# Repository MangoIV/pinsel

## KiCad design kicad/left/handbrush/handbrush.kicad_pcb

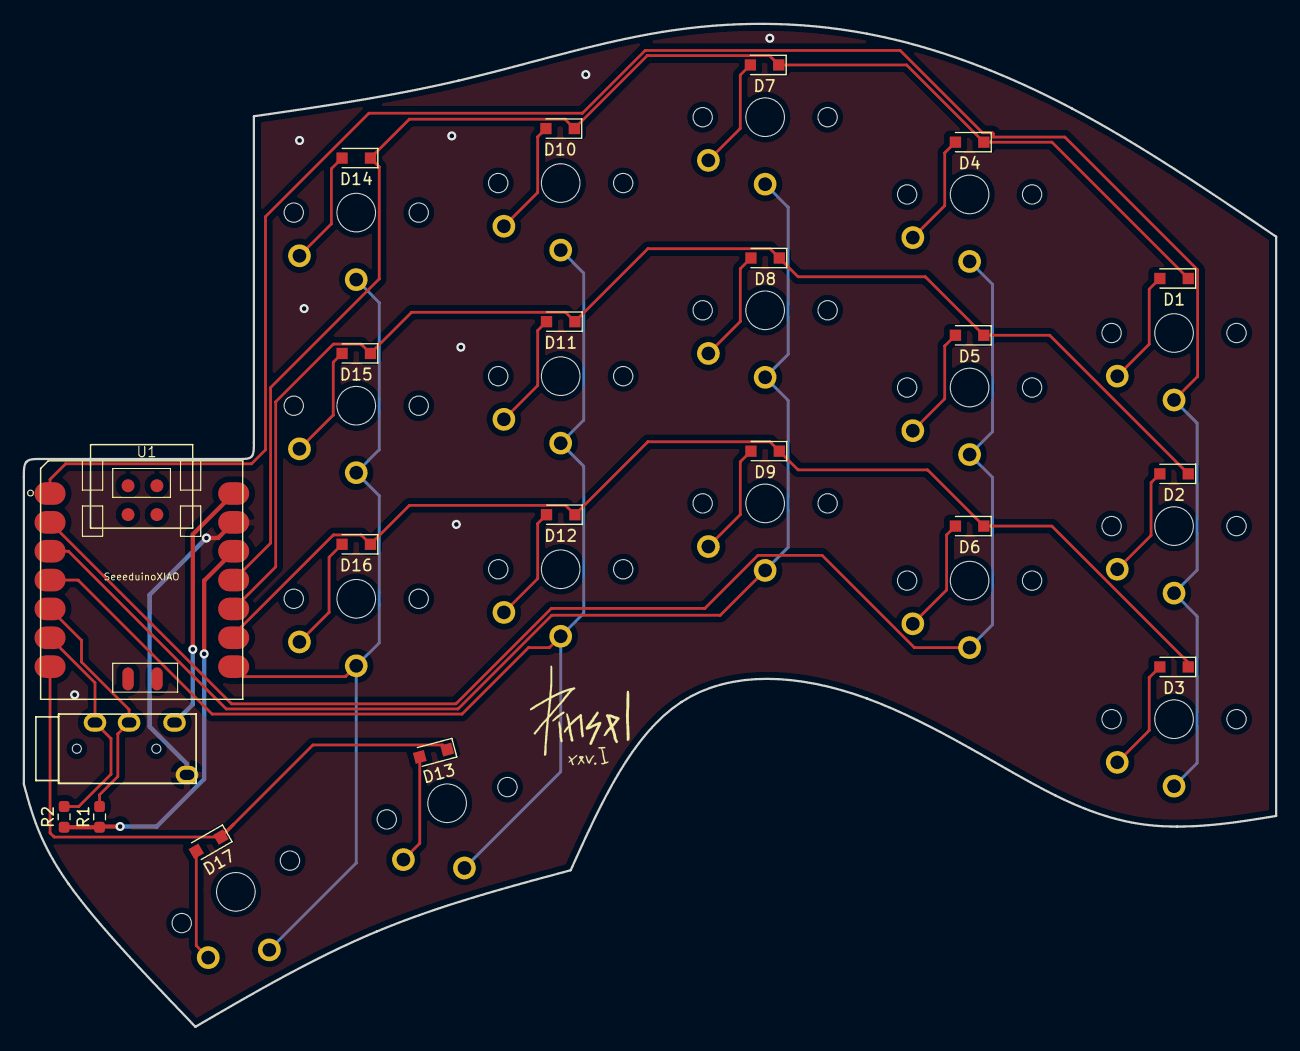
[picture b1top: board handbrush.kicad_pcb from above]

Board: 2 copper layers, 110.3 x 88.3 mm, 38 parts (0 on the bottom side), 31 nets.

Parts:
D1, D2, D3, D4, D5, D6, D7, D8, D9, D10, D11, D12, D13, D14, D15, D16, D17: D_Small; D_SOD-323_HandSoldering
J1: Conn_01x04; TRRS-PJ-320A
MX1, MX2, MX3, MX4, MX5, MX6, MX7, MX8, MX9, MX10, MX11, MX12, MX13, MX14, MX15, MX16, MX17: MX-NoLED; Choc-1u-solder
R1, R2: 4.7k; R_0603_1608Metric_Pad0.98x0.95mm_HandSolder
U1: SeeeduinoXIAO; Seeeduino XIAO-MOUDLE14P-2.54-21X17.8MM

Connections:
+3V3: R1.1, R2.1, U1.12
+5V: J1.2, U1.14
GND: J1.1, U1.13
unnamed: D1.2, MX1.2
unnamed: D2.2, MX2.2
unnamed: D3.2, MX3.2
unnamed: D4.2, MX4.2
unnamed: D5.2, MX5.2
unnamed: D6.2, MX6.2
unnamed: D7.2, MX7.2
unnamed: D8.2, MX8.2
unnamed: D9.2, MX9.2
unnamed: D10.2, MX10.2
unnamed: D11.2, MX11.2
unnamed: D12.2, MX12.2
unnamed: D13.2, MX13.2
unnamed: D14.2, MX14.2
unnamed: D15.2, MX15.2
unnamed: D16.2, MX16.2
unnamed: D17.2, MX17.2
col0: MX1.1, MX2.1, MX3.1, U1.1
col1: MX4.1, MX5.1, MX6.1, U1.2
col2: MX7.1, MX8.1, MX9.1, U1.3
col3: MX10.1, MX11.1, MX12.1, MX13.1, U1.4
col4: MX14.1, MX15.1, MX16.1, MX17.1, U1.8
row0: D1.1, D4.1, D7.1, D10.1, D14.1, U1.11
row1: D2.1, D5.1, D8.1, D11.1, D15.1, U1.10
row2: D3.1, D6.1, D9.1, D12.1, D16.1, U1.9
row3: D13.1, D17.1, U1.7
scl: J1.4, R2.2, U1.6
sda: J1.3, R1.2, U1.5

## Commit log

2021-04-12 added submodules and some parts
2021-04-12 added first part of the schematic
2021-04-30 added pinsel
